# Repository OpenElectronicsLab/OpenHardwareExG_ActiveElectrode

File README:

OpenHardwareExG_ActiveElectrode

Placing an amplifier near the skin may reduce noise pickup by the
electrode leads.

This project is in early development and is not yet ready for use.

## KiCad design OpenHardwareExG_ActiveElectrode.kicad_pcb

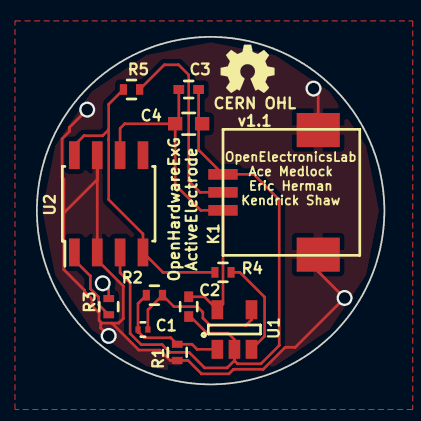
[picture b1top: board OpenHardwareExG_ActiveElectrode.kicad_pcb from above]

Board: 4 copper layers, 19.3 x 19.3 mm, 13 parts (1 on the bottom side), 10 nets.

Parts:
C1: 1nF; C_0201
C2, C3: 1uF; C_0402
C4: 10uF; C_0603
K1: CONN_3; DF50A-3P-1H
P1: CONN_1; electrode_pad
R1, R3, R5: 100; R_0402
R2, R4: 10k; R_0402
U1: LMP7715; SOT-23-5
U2: LMP7721; SOIC-8_3.9x4.9mm_Pitch1.27mm

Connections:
+5V: C2.1, C3.1, C4.1, K1.1, U1.5, U2.6
/BUFFERED_INPUT: R4.2, R5.1, U2.4, U2.8
/ELECTRODE: P1.1, R3.1
/GUARD_RING: R1.2, U2.2, U2.7
/GUARD_RING_DRIVER: C1.1, R1.1, R2.1, U1.1
/GUARD_RING_FILTERED_FEEDBACK: C1.2, R2.2, U1.4
/GUARD_RING_INPUT: R4.1, U1.3
/LINE_OUT: K1.2, R5.2
/PROTECTED_ELECTRODE: R3.2, U2.1
GND: C2.2, C3.2, C4.2, K1.3, U1.2, U2.3

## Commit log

2015-10-12 init
2015-10-12 CERN OHL v1.1
2015-10-12 first sketch
2015-10-24 first full draft of schematic
2015-10-31 Add output resistor, label, and annotate schematic
2015-10-31 added netlist and component footprints
2015-10-31 first draft of component positions
2015-10-31 improved draft of component positions
2015-10-31 experiment with 0.1" connector (too large)
2016-01-03 finish initial PCB layout
2016-01-03 fix broken trace and move labels
2016-01-03 CERN OHL v1.1 logo, and text
2016-01-03 gerbers added
2016-01-03 fixed back mask, renamed internal layers for oshpark
    Order number dTIGmO2k
2016-01-08 generated with bom2csv
    wget https://raw.githubusercontent.com/KiCad/kicad-source-mirror/master/eeschema/plugins/bom2csv.xsl
    http://og2k.com/content/how-generate-bill-materials-bom-kicad
2016-01-08 checkpoint the bom
2016-01-08 add the DF50A-3P-1H module to git
2016-01-08 update csv for mouser bom tool
2016-01-08 bom for cable
2016-02-20 update to CERN OHL v1.2 or later
2016-11-26 TODO: solder pads very small for hand-soldering
